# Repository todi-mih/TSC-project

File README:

Project for E-book made in fusion

Diagrama:
(its in the images folder)

_______
Hardware Modules Overview
ESP32-C6-WROOM-1-N8 – Core Microcontroller
Power Supply: 3.3V
Communication Protocols: SPI, I2C, UART, GPIO
Pin Mapping: Below, each module's interface is connected to the respective microcontroller pins.

USB-C Connector + ESD Protection
Main input for power and data transfer
TVS diodes included for electrostatic discharge (ESD) protection

LiPo Battery Fuel Gauge
Built-In charging controller
IC: MAX17048G+T10 for battery level monitoring
I2C Interface: SCL/SDA for communication with the Battery ChargeLevel IC
Qwiic / Stemma QT Connector for communication via I2C

Reset and Boot Buttons
BOOT: IO9
RESET: EN (Enable)
Reverse polarity protection diodes for safety

LDO Voltage Regulator
Converts 5V to 3.3V, providing power to the ESP32-C6 and connected peripherals

External Flash - NOR Flash 64MB
Connection Type: SPI
FLASH_CS: IO11
Shared SPI Lines: MOSI, MISO, SCK (with SD card and e-paper)

Environmental Sensor - BME688
Protocol: I2C (shared with RTC)
Voltage Supply: 3.3V
Pin Assignments: SDA, SCL

E-Paper Display
Connection Type: SPI
EPD_CS: IO10
EPD_DC: IO5
EPD_RST: IO23
EPD_BUSY: IO3
Shared SPI Lines: MOSI, SCK with SD Card

RTC Module - DS3231SN
Connection Type: I2C
SCL: IO22
SDA: IO21
INT_RTC: IO8
32KHZ: IO1
RTC_RST: IO18

SD Card Interface
Connection Type: SPI
SS_SD: IO4
MOSI: IO7
MISO: IO2
SCK: IO6

SPI Line Protection
Safeguards the SPI communication lines used by external modules like the SD card, e-paper display, and external flash
______

ESP32-C6 PINS
Protocol	ESP32-C6 Assigned Pins		Attached Devices
USB				GPIO13, GPIO12			Power supply & host communication
I2C				GPIO22, GPIO24			Environmental sensor (BME688), RTC, Battery voltage monitor
SPI			  GPIO7, GPIO2, GPIO6		E-paper display, NOR flash memory, SD storage
UART			GPIO16, GPIO17			Debugging / Firmware change
GPIO			GPIO0...GPIO23			Buttons, indicator outputs

BOM , links , datasheets
BUTTON_CUSYOMV1 https://eu.mouser.com/ProductDetail/Omron-Electronics/B3F-1000S?qs=C6KiJco3hx0Z3qfxWTJOrg%3D%3D
https://eu.mouser.com/datasheet/2/307/en_b3f-13826.pdf

100nF capacitor https://store.comet.srl.ro/Catalogue/Product/48939/ https://store.comet.bg/download-file.php?id=11
CPH3225A        https://eu.mouser.com/ProductDetail/Seiko-Semiconductors/CPH3225Aqs=3etwrb1wR%252BhUOph6lAO7eg%3D%3D
https://ro.mouser.com/datasheet/2/360/Seiko_Instruments_MicroBattery_E_20230330_2024Jan_-3561061.pdf
1.7uF capacitor https://store.comet.srl.ro/Catalogue/Product/5163462/ https://store.comet.bg/download-file.php?id=25117
USBLC6-2SC6Y    https://eu.mouser.com/ProductDetail/STMicroelectronics/USBLC6-2SC6Yqs=gNDSiZmRJS%2FOgDexvXkdow%3D%3D
https://ro.mouser.com/datasheet/2/389/usblc6_2sc6y-1852505.pdf
PGB1010603MR    https://eu.mouser.com/ProductDetail/Littelfuse/PGB1010603MR?qs=gu7KAQ731URLg4GSnNNN7Q%3D%3D
https://www.littelfuse.com/assetdocs/pulseguard-esd-suppressors-pgb1-datasheet?assetguid=8a337998-d54d-466b-be4e-dc5bcd1f9321
MBR0530         https://eu.mouser.com/ProductDetail/onsemi/MBR0530T3G?qs=3JMERSakebpEmdUS6GetdQ%3D%3D
https://www.littelfuse.com/assetdocs/pulseguard-esd-suppressors-pgb1-datasheet?assetguid=8a337998-d54d-466b-be4e-dc5bcd1f9321
TP20R           https://eu.mouser.com/ProductDetail/KOA-Speer/RN73R1ETTP20R0D50?qs=vLWxofP3U2xF4IfSiw9UAw%3D%3D
DS3231SN#       https://eu.mouser.com/ProductDetail/Analog-Devices-Maxim-Integrated/DS3231SN?qs=1eQvB6Dk1vhUlr8%2FOrV0Fw%3D%3D
https://www.koaspeer.com/pdfs/RN73R.pdf
W25Q512JVEIQ    https://eu.mouser.com/ProductDetail/Winbond/W25Q512JVEIQ?qs=l7cgNqFNU1jw6svr3at6tA%3D%3D
https://ro.mouser.com/datasheet/2/949/Winbond_W25Q512JV_Datasheet-3240039.pdf
MAX17048G+T10   https://eu.mouser.com/ProductDetail/Analog-Devices-Maxim-Integrated/MAX17048G%2bT10?qs=D7PJwyCwLAoGnnn8jEPRBQ%3D%3D
https://ro.mouser.com/datasheet/2/609/MAX17048_MAX17049-3469099.pdf
USBLC6-2SC6Y    https://eu.mouser.com/ProductDetail/STMicroelectronics/USBLC6-2SC6Y?qs=gNDSiZmRJS%2FOgDexvXkdow%3D%3D
https://ro.mouser.com/datasheet/2/389/usblc6_2sc6y-1852505.pdf
DMG2305UX-7     https://eu.mouser.com/ProductDetail/Diodes-Incorporated/DMG2305UX-7?qs=L1DZKBg7t5F%2FNBHrjfxC%252Bg%3D%3D
https://www.diodes.com/assets/Datasheets/DMG2305UX.pdf
XC6220A331MR-G  https://eu.mouser.com/ProductDetail/Torex-Semiconductor/XC6220A331MR-G?qs=AsjdqWjXhJ8ZSWznL1J0gg%3D%3D
https://ro.mouser.com/datasheet/2/760/xc6220-3371556.pdf
SI1308EDL-T1-BE3  https://eu.mouser.com/ProductDetail/Vishay-Siliconix/SI1308EDL-T1-BE3?qs=zW32dvEIR3shhEGZ2ACCcQ%3D%3D
https://www.vishay.com/doc?63399
MCP73831        https://eu.mouser.com/ProductDetail/Microchip-Technology/MCP73831T-2ACI-OT?qs=yUQqVecv4qvbBQBGbHx0Mw%3D%3D
https://ro.mouser.com/datasheet/2/268/MCP73831_Family_Data_Sheet_DS20001984H-3441711.pdf
ESP32-C6-WROOM-1-N8   https://eu.mouser.com/ProductDetail/Espressif-Systems/ESP32-C6-WROOM-1-N8?qs=8Wlm6%252BaMh8ST02Gmwp74cw%3D%3D
https://ro.mouser.com/datasheet/2/891/Espressif_ESP32_C6_WROOM_1__Datasheet_V0_1_PRELIMI-3239987.pdf
BD5229G     https://eu.mouser.com/ProductDetail/ROHM-Semiconductor/BD5229G-1TR?qs=sGAEpiMZZMutXGli8Ay4kGHG90gjHVFpj6WJfKJTe9w%3D
https://fscdn.rohm.com/en/products/databook/datasheet/ic/power/voltage_detector/bd52xxg-1-e.pdf
FH34SRJ-24S-0.5SH_99_   https://eu.mouser.com/ProductDetail/Hirose-Connector/FH34SRJ-24S-0.5SH50?qs=iyLo5FA4poC8fzWlavnA7A%3D%3D
https://ro.mouser.com/datasheet/2/185/FH34SRJ_24S_0_5SH_50__CL0580_1255_6_50_2DDrawing_0-1615030.pdf
BME688     https://eu.mouser.com/ProductDetail/Bosch-Sensortec/BME688?qs=IS%252B4QmGtzzqQoVDscqwx3A%3D%3D
https://ro.mouser.com/datasheet/2/783/bst_bme688_fl000-2307034.pdf

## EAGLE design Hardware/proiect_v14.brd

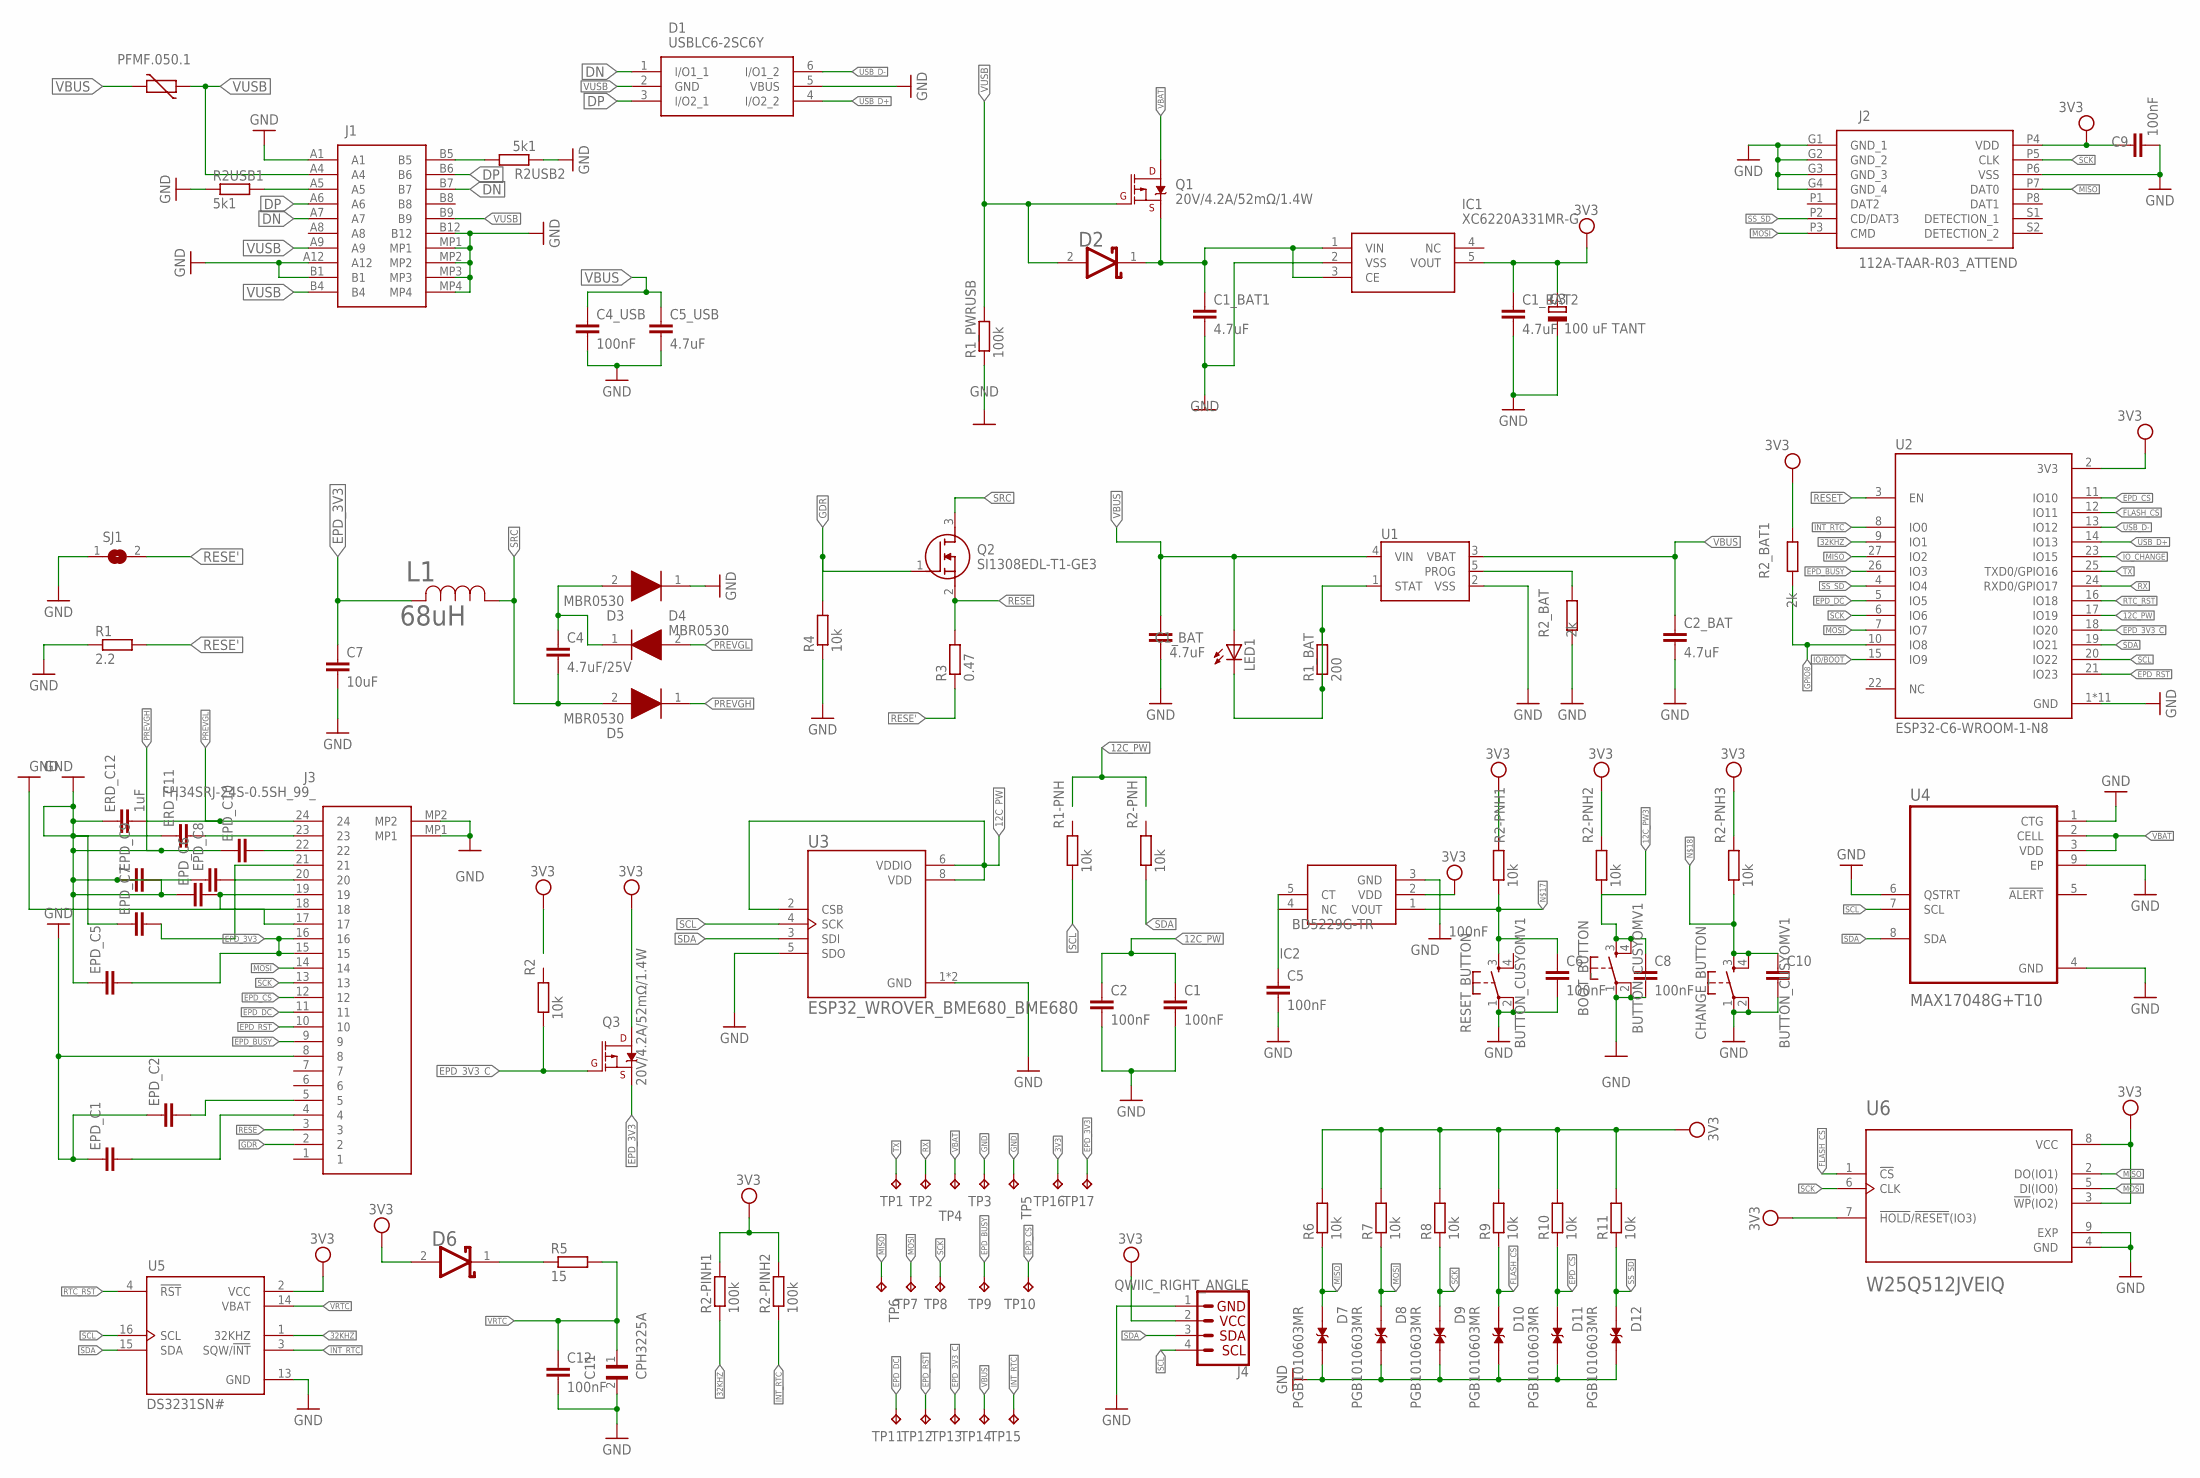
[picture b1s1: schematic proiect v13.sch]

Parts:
BOOT_BUTTON: BUTTON_CUSYOMV1; MYBUTTON
C1, C2, C4_USB, C5, C6, C8, C9, C10: 100nF; EAGLE-LTSPICE_C0402
C1_BAT, C1_BAT1, C1_BAT2, C2_BAT, C5_USB: 4.7uF; EAGLE-LTSPICE_C0402
C3: 100 uF TANT; RCL_CT3528
C4: 4.7uF/25V; EAGLE-LTSPICE_C0402
C7: 10uF; EAGLE-LTSPICE_C0402
C11: CPH3225A; CAPCP3225X100N
C12: 100nF; ESP32_WROVER_EAGLE-LTSPICE_C0402
CHANGE_BUTTON: BUTTON_CUSYOMV1; MYBUTTON
D1: USBLC6-2SC6Y; SOT95P280X145-6N
D2, D6: ESP32_WROVER_AVX---SD0805S020S1R0_AVX_SD0805S020S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; ESP32_WROVER_AVX---SD0805S020S1R0_AVX_SD0805S020S1R0_0
D3, D4, D5: MBR0530; SOD3716X135N
D7, D8, D9, D10, D11, D12: PGB1010603MR; DIOC1608X36N
EPD_C1, EPD_C2, EPD_C5, EPD_C6, EPD_C7, EPD_C8, EPD_C9: EAGLE-LTSPICE_CC0402; EAGLE-LTSPICE_C0402
EPD_C10: ESP32_WROVER_EAGLE-LTSPICE_CC0402; ESP32_WROVER_EAGLE-LTSPICE_C0402
ERD_C11: ESP32_WROVER_EAGLE-LTSPICE_CC0402; ESP32_WROVER_EAGLE-LTSPICE_C0402
ERD_C12: 1uF; ESP32_WROVER_EAGLE-LTSPICE_C0402
IC1: XC6220A331MR-G; SOT95P280X120-5N
IC2: BD5229G-TR; SOT95P280X125-5N
J1: SAMACSYS_PARTS_USB4110-GF-A; SAMACSYS_PARTS_USB4110GFA
J2: 112A-TAAR-R03_ATTEND; 112ATAARR03ATTEND
J3: FH34SRJ-24S-0.5SH_99_; FH34SRJ24S05SH99
J4: QWIIC_RIGHT_ANGLE; JST04_1MM_RA
L1: 68uH; IND_4828-WE-TPC_WRE
LED1: ADAFRUIT_LEDCHIP-LED0603; ADAFRUIT_CHIP-LED0603
PFMF.050.1: ESP32C6_VARISTORCN1812; ESP32C6_VARISTOR_CT/CN1812
Q1, Q3: 20V/4.2A/52mΩ/1.4W; ESP32_WROVER_SPARKFUN-DISCRETESEMI_SOT23-3
Q2: SI1308EDL-T1-GE3; SOT65P210X110-3N
R1: 2.2; ESP32_WROVER_EAGLE-LTSPICE_R0402
R1-PNH, R2, R2-PNH, R2-PNH1, R2-PNH2, R2-PNH3, R4, R6, R7, R8, R9, R10, R11: 10k; ESP32_WROVER_EAGLE-LTSPICE_R0402
R1_BAT: 200; ESP32_WROVER_EAGLE-LTSPICE_R0402
R1_PWRUSB, R2-PINH1, R2-PINH2: 100k; ESP32_WROVER_EAGLE-LTSPICE_R0402
R2USB1, R2USB2: 5k1; ESP32_WROVER_EAGLE-LTSPICE_R0402
R2_BAT, R2_BAT1: 2k; ESP32_WROVER_EAGLE-LTSPICE_R0402
R3: 0.47; ESP32_WROVER_EAGLE-LTSPICE_R0402
R5: 15; ESP32_WROVER_EAGLE-LTSPICE_R0402
RESET_BUTTON: BUTTON_CUSYOMV1; MYBUTTON
SJ1: SJ
TP1, TP2, TP3, TP4, TP5, TP6, TP7, TP8, TP9, TP10, TP11, TP12, TP13, TP14, TP15, TP16, TP17: TPTP20R; TP20R
U1: ESP32_WROVER_SPARKFUN-IC-POWER_MCP73831; ESP32_WROVER_SPARKFUN-IC-POWER_SOT23-5
U2: ESP32-C6-WROOM-1-N8; XCVR_ESP32-C6-WROOM-1-N8
U3: ESP32_WROVER_BME680_BME680; ESP32_WROVER_BME680_PSON80P300X300X100-8N
U4: MAX17048G+T10; SON50P200X200X80-9N
U5: DS3231SN#; SOIC127P1032X265-16N
U6: W25Q512JVEIQ; SON127P600X800X80-9N

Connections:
3V3: C1_BAT2.1, C3.+, C9.1, D6.2 (ANODE), IC1.5 (VOUT), IC2.2 (VDD), J2.P4 (VDD), J4.2, Q3.3 (D), R2-PINH1.2, R2-PINH2.2, R2-PNH1.2, R2-PNH2.2, R2-PNH3.2, R2_BAT1.2, R6.2, R7.2, R8.2, R9.2, R10.2, R11.2, TP16.TP, U2.2 (3V3), U5.2 (VCC), U6.3 (!WP!(IO2)), U6.7 (!HOLD!/!RESET!(IO3)), U6.8 (VCC)
12C_PW: C1.1, C2.1, U2.17 (IO19), U3.2 (CSB), U3.6 (VDDIO), U3.8 (VDD)
12C_PW1: C5.1, IC2.5 (CT)
12C_PW3: BOOT_BUTTON.3, BOOT_BUTTON.4, C8.1, R2-PNH2.1
32KHZ: R2-PINH1.1, U2.9 (IO1), U5.1 (32KHZ)
DN: J1.A7, J1.B6
DP: J1.A6, J1.B7
EPD_3V3: C7.1, EPD_C5.2, J3.15, J3.16, L1.2, Q3.2 (S), TP17.TP
EPD_3V3_C: Q3.1 (G), R2.1, TP13.TP, U2.18 (IO20)
EPD_BUSY: J3.9, TP9.TP, U2.26 (IO3)
EPD_CS: D11.1, J3.12, R10.1, TP10.TP, U2.11 (IO10)
EPD_DC: J3.11, TP11.TP, U2.5 (IO5)
EPD_RST: J3.10, TP12.TP, U2.21 (IO23)
FLASH_CS: D10.1, R9.1, U2.12 (IO11), U6.1 (!CS)
GDR: J3.2, Q2.1 (G), R4.2
GND: BOOT_BUTTON.1, BOOT_BUTTON.2, C1.2, C1_BAT.2, C1_BAT1.2, C1_BAT2.2, C2.2, C2_BAT.2, C3.-, C4_USB.2, C5.2, C5_USB.2, C6.2, C7.2, C8.2, C9.2, C10.2, C11.2, C12.2, CHANGE_BUTTON.1, CHANGE_BUTTON.2, D1.5 (VBUS), D3.1 (K), D7.2, D8.2, D9.2, D10.2, D11.2, D12.2, EPD_C1.1, EPD_C2.1, IC1.2 (VSS), IC2.3 (GND), J1.A1, J1.A12, J1.B1, J1.B12, J1.MP1, J1.MP2, J1.MP3, J1.MP4, J2.G1 (GND_1), J2.G2 (GND_2), J2.G3 (GND_3), J2.G4 (GND_4), J2.P6 (VSS), J3.8, J3.17, J3.MP1, J3.MP2, J4.1, R1.1, R1_PWRUSB.1, R2USB1.1, R2USB2.1, R2_BAT.1, R4.1, RESET_BUTTON.1, RESET_BUTTON.2, SJ1.1, TP3.TP, TP5.TP, U1.2 (VSS), U2.1 (GND), U2.28 (GND), U2.29_1 (GND), U2.29_2 (GND), U2.29_3 (GND), U2.29_4 (GND), U2.29_5 (GND), U2.29_6 (GND), U2.29_7 (GND), U2.29_8 (GND), U2.29_9 (GND), U3.1 (GND), U3.5 (SDO), U3.7 (GND), U4.1 (CTG), U4.4 (GND), U4.6 (QSTRT), U4.9 (EP), U5.13 (GND), U6.4 (GND), U6.9 (EXP)
GPIO8: R2_BAT1.1, U2.10 (IO8)
INT_RTC: R2-PINH2.1, TP15.TP, U2.8 (IO0), U5.3 (SQW/!INT)
IO/BOOT: U2.15 (IO9)
IO_CHANGE: U2.23 (IO15)
MISO: D7.1, J2.P7 (DAT0), R6.1, TP6.TP, U2.27 (IO2), U6.2 (DO(IO1))
MOSI: D8.1, J2.P3 (CMD), J3.14, R7.1, TP7.TP, U2.7 (IO7), U6.5 (DI(IO0))
unnamed: J1.A5, R2USB1.2
unnamed: J1.B5, R2USB2.2
unnamed: C4_USB.1, C5_USB.1
unnamed: C1_BAT1.1, D2.1 (CATHODE), IC1.1 (VIN), IC1.3 (CE), Q1.2 (S)
unnamed: D2.2 (ANODE), Q1.1 (G), R1_PWRUSB.2
unnamed: R2_BAT.2, U1.5 (PROG)
unnamed: C4.1, D3.2 (A), D4.1 (K)
unnamed: EPD_C1.2, J3.4
unnamed: EPD_C2.2, J3.5
unnamed: C6.1, IC2.1 (VOUT), R2-PNH1.1, RESET_BUTTON.3
unnamed: C10.1, CHANGE_BUTTON.3, CHANGE_BUTTON.4, R2-PNH3.1
unnamed: D6.1 (CATHODE), R5.1
unnamed: EPD_C8.2, J3.20
unnamed: EPD_C7.2, J3.21
unnamed: EPD_C6.2, J3.18, J3.19
unnamed: EPD_C10.2, J3.22
unnamed: ERD_C11.2, J3.23
PREVGH: D5.1 (K), EPD_C5.1, EPD_C6.1, EPD_C7.1, EPD_C8.1, EPD_C9.1, EPD_C9.2, EPD_C10.1, ERD_C11.1, ERD_C12.1
PREVGL: D4.2 (A), ERD_C12.2, J3.24
RESE: J3.3, Q2.2 (S), R3.2
RESE': R1.2, R3.1, SJ1.2
RESE'1: LED1.C, R1_BAT.1, R1_BAT.2, U1.1 (STAT)
RESET: U2.3 (EN)
RX: TP2.TP, U2.24 (RXD0/GPIO17)
SCK: D9.1, J2.P5 (CLK), J3.13, R8.1, TP8.TP, U2.6 (IO6), U6.6 (CLK)
SCL: J4.4, R1-PNH.1, U2.20 (IO22), U3.4 (SCK), U4.7 (SCL), U5.16 (SCL)
SDA: J4.3, R2-PNH.1, U2.19 (IO21), U3.3 (SDI), U4.8 (SDA), U5.15 (SDA)
SRC: C4.2, D5.2 (A), L1.1, Q2.3 (D)
SS_SD: D12.1, J2.P2 (CD/DAT3), R11.1, U2.4 (IO4)
TX: TP1.TP, U2.25 (TXD0/GPIO16)
VBAT: Q1.3 (D), TP4.TP, U4.2 (CELL), U4.3 (VDD)
VBUS: C1_BAT.1, C2_BAT.1, LED1.A, TP14.TP, U1.3 (VBAT), U1.4 (VIN)
VRTC: C11.1, C12.1, R5.2, U5.14 (VBAT)
VUSB: J1.A4, PFMF.050.1.1

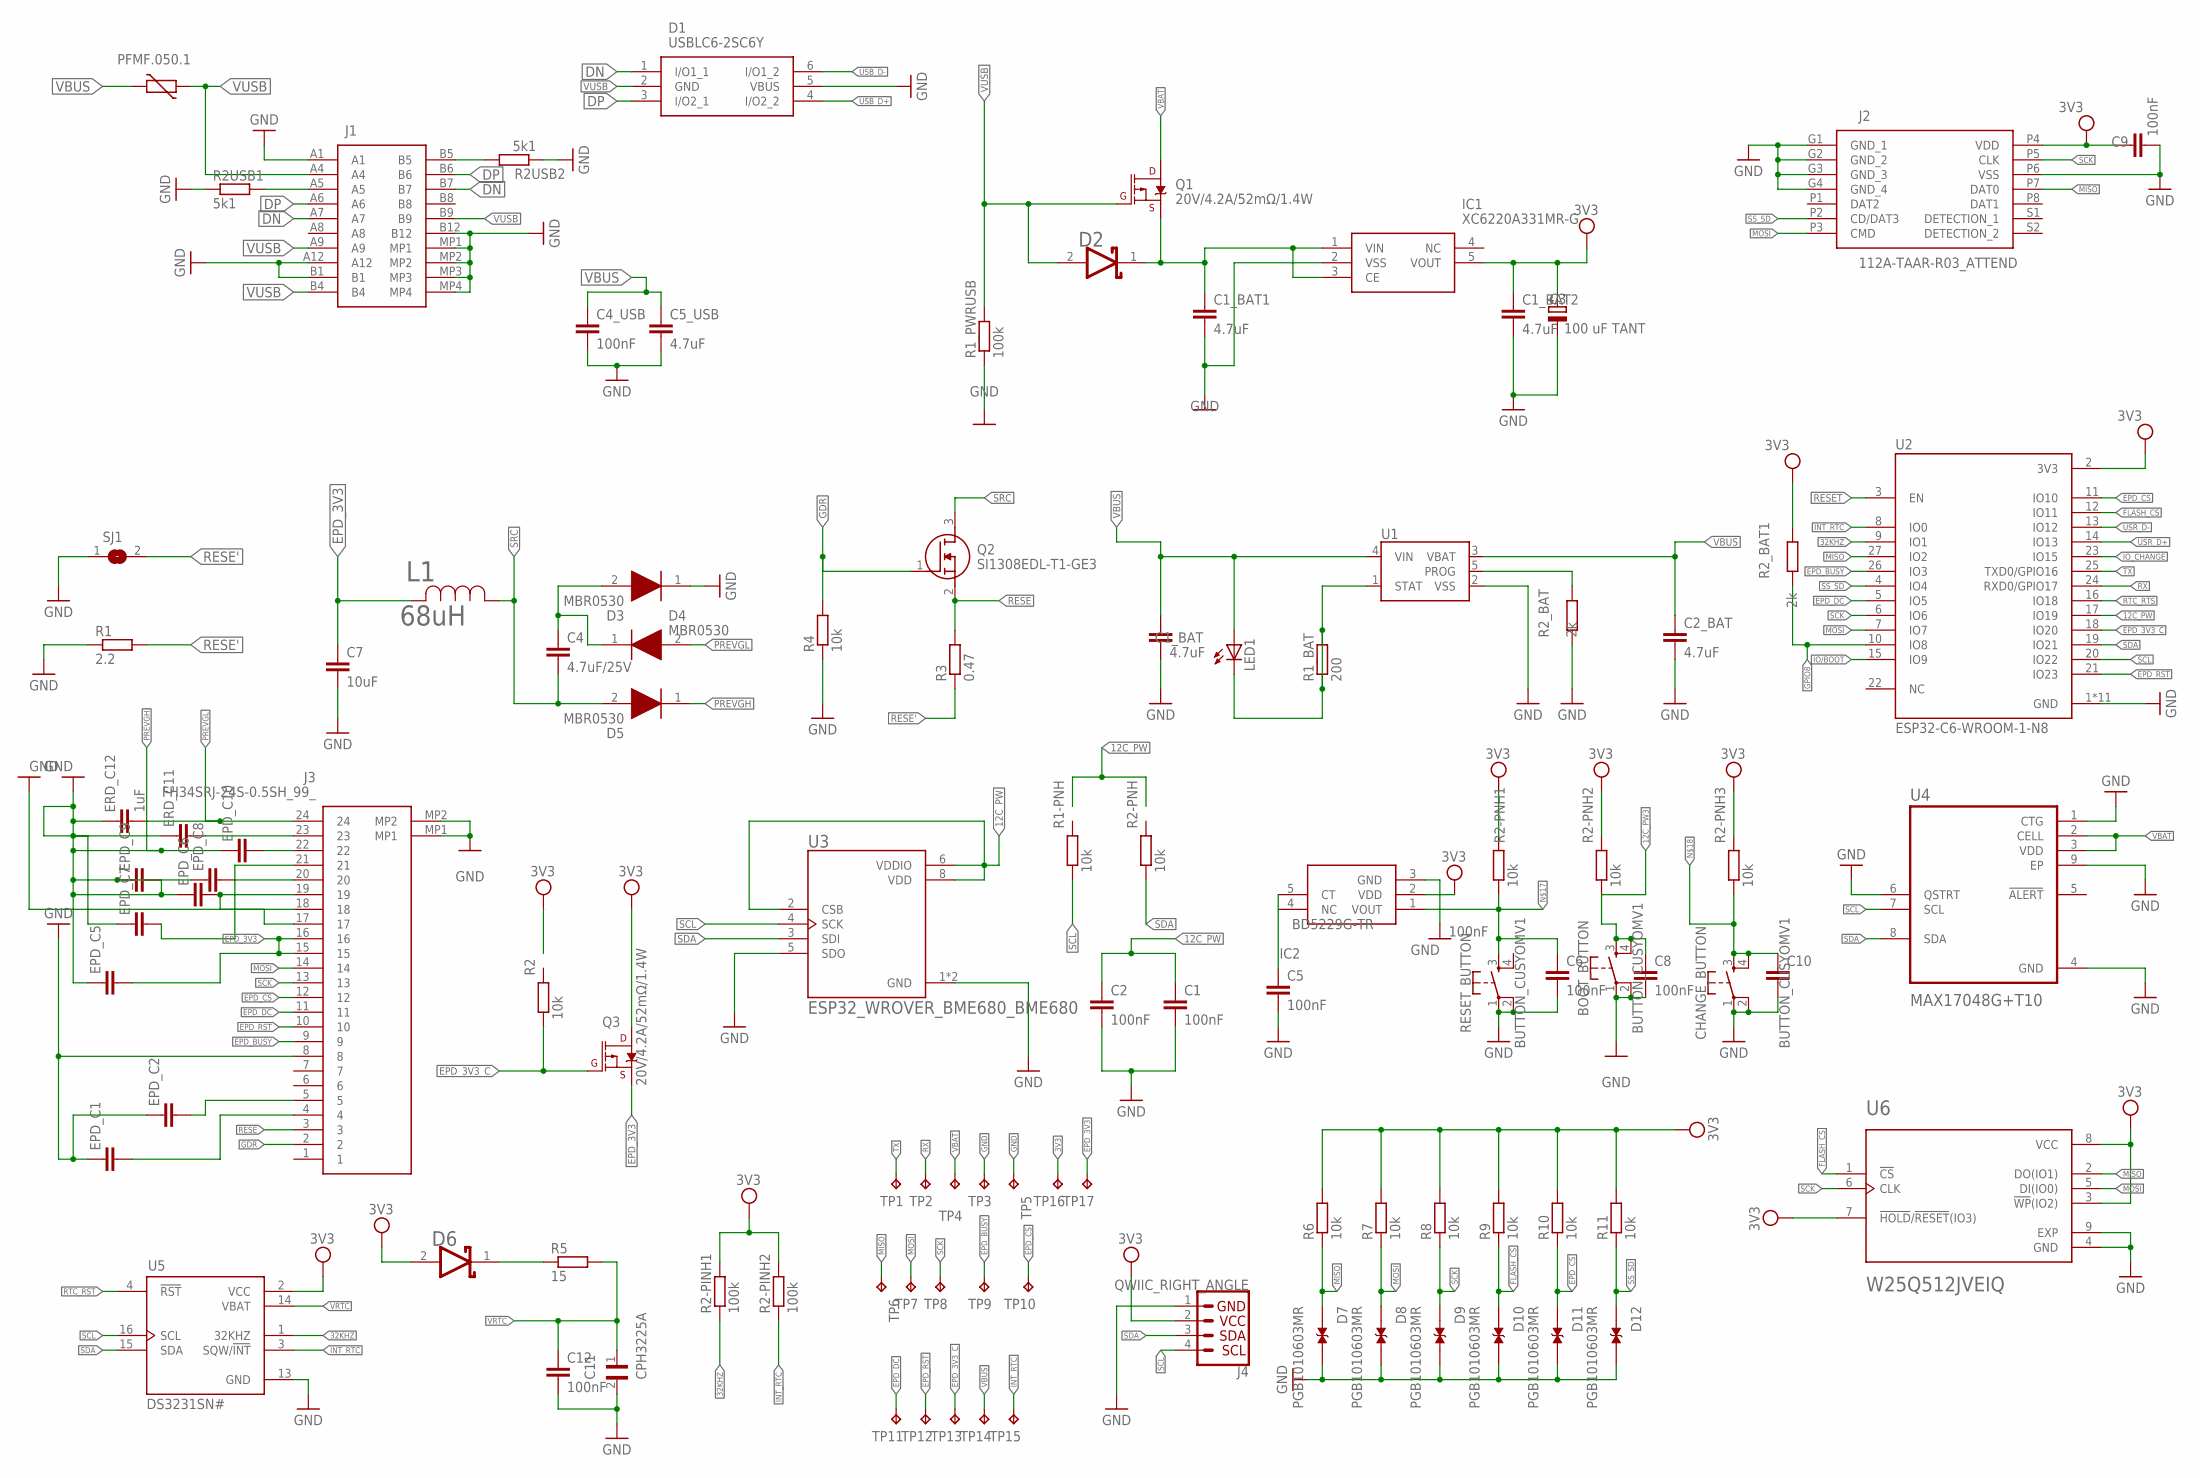
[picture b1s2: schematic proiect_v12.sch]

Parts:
BOOT_BUTTON: BUTTON_CUSYOMV1; MYBUTTON
C1, C2, C4_USB, C5, C6, C8, C9, C10: 100nF; EAGLE-LTSPICE_C0402
C1_BAT, C1_BAT1, C1_BAT2, C2_BAT, C5_USB: 4.7uF; EAGLE-LTSPICE_C0402
C3: 100 uF TANT; RCL_CT3528
C4: 4.7uF/25V; EAGLE-LTSPICE_C0402
C7: 10uF; EAGLE-LTSPICE_C0402
C11: CPH3225A; CAPCP3225X100N
C12: 100nF; ESP32_WROVER_EAGLE-LTSPICE_C0402
CHANGE_BUTTON: BUTTON_CUSYOMV1; MYBUTTON
D1: USBLC6-2SC6Y; SOT95P280X145-6N
D2, D6: ESP32_WROVER_AVX---SD0805S020S1R0_AVX_SD0805S020S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; ESP32_WROVER_AVX---SD0805S020S1R0_AVX_SD0805S020S1R0_0
D3, D4, D5: MBR0530; SOD3716X135N
D7, D8, D9, D10, D11, D12: PGB1010603MR; DIOC1608X36N
EPD_C1, EPD_C2, EPD_C5, EPD_C6, EPD_C7, EPD_C8, EPD_C9: EAGLE-LTSPICE_CC0402; EAGLE-LTSPICE_C0402
EPD_C10: ESP32_WROVER_EAGLE-LTSPICE_CC0402; ESP32_WROVER_EAGLE-LTSPICE_C0402
ERD_C11: ESP32_WROVER_EAGLE-LTSPICE_CC0402; ESP32_WROVER_EAGLE-LTSPICE_C0402
ERD_C12: 1uF; ESP32_WROVER_EAGLE-LTSPICE_C0402
IC1: XC6220A331MR-G; SOT95P280X120-5N
IC2: BD5229G-TR; SOT95P280X125-5N
J1: SAMACSYS_PARTS_USB4110-GF-A; SAMACSYS_PARTS_USB4110GFA
J2: 112A-TAAR-R03_ATTEND; 112ATAARR03ATTEND
J3: FH34SRJ-24S-0.5SH_99_; FH34SRJ24S05SH99
J4: QWIIC_RIGHT_ANGLE; JST04_1MM_RA
L1: 68uH; IND_4828-WE-TPC_WRE
LED1: ADAFRUIT_LEDCHIP-LED0603; ADAFRUIT_CHIP-LED0603
PFMF.050.1: ESP32C6_VARISTORCN1812; ESP32C6_VARISTOR_CT/CN1812
Q1, Q3: 20V/4.2A/52mΩ/1.4W; ESP32_WROVER_SPARKFUN-DISCRETESEMI_SOT23-3
Q2: SI1308EDL-T1-GE3; SOT65P210X110-3N
R1: 2.2; ESP32_WROVER_EAGLE-LTSPICE_R0402
R1-PNH, R2, R2-PNH, R2-PNH1, R2-PNH2, R2-PNH3, R4, R6, R7, R8, R9, R10, R11: 10k; ESP32_WROVER_EAGLE-LTSPICE_R0402
R1_BAT: 200; ESP32_WROVER_EAGLE-LTSPICE_R0402
R1_PWRUSB, R2-PINH1, R2-PINH2: 100k; ESP32_WROVER_EAGLE-LTSPICE_R0402
R2USB1, R2USB2: 5k1; ESP32_WROVER_EAGLE-LTSPICE_R0402
R2_BAT, R2_BAT1: 2k; ESP32_WROVER_EAGLE-LTSPICE_R0402
R3: 0.47; ESP32_WROVER_EAGLE-LTSPICE_R0402
R5: 15; ESP32_WROVER_EAGLE-LTSPICE_R0402
RESET_BUTTON: BUTTON_CUSYOMV1; MYBUTTON
SJ1: SJ
TP1, TP2, TP3, TP4, TP5, TP6, TP7, TP8, TP9, TP10, TP11, TP12, TP13, TP14, TP15, TP16, TP17: TPTP20R; TP20R
U1: ESP32_WROVER_SPARKFUN-IC-POWER_MCP73831; ESP32_WROVER_SPARKFUN-IC-POWER_SOT23-5
U2: ESP32-C6-WROOM-1-N8; XCVR_ESP32-C6-WROOM-1-N8
U3: ESP32_WROVER_BME680_BME680; ESP32_WROVER_BME680_PSON80P300X300X100-8N
U4: MAX17048G+T10; SON50P200X200X80-9N
U5: DS3231SN#; SOIC127P1032X265-16N
U6: W25Q512JVEIQ; SON127P600X800X80-9N

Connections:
3V3: C1_BAT2.1, C3.+, C9.1, D6.2 (ANODE), IC1.5 (VOUT), IC2.2 (VDD), J2.P4 (VDD), J4.2, Q3.3 (D), R2-PINH1.2, R2-PINH2.2, R2-PNH1.2, R2-PNH2.2, R2-PNH3.2, R2_BAT1.2, R6.2, R7.2, R8.2, R9.2, R10.2, R11.2, TP16.TP, U2.2 (3V3), U5.2 (VCC), U6.3 (!WP!(IO2)), U6.7 (!HOLD!/!RESET!(IO3)), U6.8 (VCC)
12C_PW: C1.1, C2.1, U2.17 (IO19), U3.2 (CSB), U3.6 (VDDIO), U3.8 (VDD)
12C_PW1: C5.1, IC2.5 (CT)
12C_PW3: BOOT_BUTTON.3, BOOT_BUTTON.4, C8.1, R2-PNH2.1
32KHZ: R2-PINH1.1, U2.9 (IO1), U5.1 (32KHZ)
DN: J1.A7, J1.B6
DP: J1.A6, J1.B7
EPD_3V3: C7.1, EPD_C5.2, J3.15, J3.16, L1.2, Q3.2 (S), TP17.TP
EPD_3V3_C: Q3.1 (G), R2.1, TP13.TP, U2.18 (IO20)
EPD_BUSY: J3.9, TP9.TP, U2.26 (IO3)
EPD_CS: D11.1, J3.12, R10.1, TP10.TP, U2.11 (IO10)
EPD_DC: J3.11, TP11.TP, U2.5 (IO5)
EPD_RST: J3.10, TP12.TP, U2.21 (IO23)
FLASH_CS: D10.1, R9.1, U2.12 (IO11), U6.1 (!CS)
GDR: J3.2, Q2.1 (G), R4.2
GND: BOOT_BUTTON.1, BOOT_BUTTON.2, C1.2, C1_BAT.2, C1_BAT1.2, C1_BAT2.2, C2.2, C2_BAT.2, C3.-, C4_USB.2, C5.2, C5_USB.2, C6.2, C7.2, C8.2, C9.2, C10.2, C11.2, C12.2, CHANGE_BUTTON.1, CHANGE_BUTTON.2, D1.5 (VBUS), D3.1 (K), D7.2, D8.2, D9.2, D10.2, D11.2, D12.2, EPD_C1.1, EPD_C2.1, IC1.2 (VSS), IC2.3 (GND), J1.A1, J1.A12, J1.B1, J1.B12, J1.MP1, J1.MP2, J1.MP3, J1.MP4, J2.G1 (GND_1), J2.G2 (GND_2), J2.G3 (GND_3), J2.G4 (GND_4), J2.P6 (VSS), J3.8, J3.17, J3.MP1, J3.MP2, J4.1, R1.1, R1_PWRUSB.1, R2USB1.1, R2USB2.1, R2_BAT.1, R4.1, RESET_BUTTON.1, RESET_BUTTON.2, SJ1.1, TP3.TP, TP5.TP, U1.2 (VSS), U2.1 (GND), U2.28 (GND), U2.29_1 (GND), U2.29_2 (GND), U2.29_3 (GND), U2.29_4 (GND), U2.29_5 (GND), U2.29_6 (GND), U2.29_7 (GND), U2.29_8 (GND), U2.29_9 (GND), U3.1 (GND), U3.5 (SDO), U3.7 (GND), U4.1 (CTG), U4.4 (GND), U4.6 (QSTRT), U4.9 (EP), U5.13 (GND), U6.4 (GND), U6.9 (EXP)
GPIO8: R2_BAT1.1, U2.10 (IO8)
INT_RTC: R2-PINH2.1, TP15.TP, U2.8 (IO0), U5.3 (SQW/!INT)
IO/BOOT: U2.15 (IO9)
IO_CHANGE: U2.23 (IO15)
MISO: D7.1, J2.P7 (DAT0), R6.1, TP6.TP, U2.27 (IO2), U6.2 (DO(IO1))
MOSI: D8.1, J2.P3 (CMD), J3.14, R7.1, TP7.TP, U2.7 (IO7), U6.5 (DI(IO0))
unnamed: J1.A5, R2USB1.2
unnamed: J1.B5, R2USB2.2
unnamed: C4_USB.1, C5_USB.1
unnamed: C1_BAT1.1, D2.1 (CATHODE), IC1.1 (VIN), IC1.3 (CE), Q1.2 (S)
unnamed: D2.2 (ANODE), Q1.1 (G), R1_PWRUSB.2
unnamed: R2_BAT.2, U1.5 (PROG)
unnamed: C4.1, D3.2 (A), D4.1 (K)
unnamed: EPD_C1.2, J3.4
unnamed: EPD_C2.2, J3.5
unnamed: C6.1, IC2.1 (VOUT), R2-PNH1.1, RESET_BUTTON.3
unnamed: C10.1, CHANGE_BUTTON.3, CHANGE_BUTTON.4, R2-PNH3.1
unnamed: D6.1 (CATHODE), R5.1
unnamed: EPD_C8.2, J3.20
unnamed: EPD_C7.2, J3.21
unnamed: EPD_C6.2, J3.18, J3.19
unnamed: EPD_C10.2, J3.22
unnamed: ERD_C11.2, J3.23
PREVGH: D5.1 (K), EPD_C5.1, EPD_C6.1, EPD_C7.1, EPD_C8.1, EPD_C9.1, EPD_C9.2, EPD_C10.1, ERD_C11.1, ERD_C12.1
PREVGL: D4.2 (A), ERD_C12.2, J3.24
RESE: J3.3, Q2.2 (S), R3.2
RESE': R1.2, R3.1, SJ1.2
RESE'1: LED1.C, R1_BAT.1, R1_BAT.2, U1.1 (STAT)
RESET: U2.3 (EN)
RX: TP2.TP, U2.24 (RXD0/GPIO17)
SCK: D9.1, J2.P5 (CLK), J3.13, R8.1, TP8.TP, U2.6 (IO6), U6.6 (CLK)
SCL: J4.4, R1-PNH.1, U2.20 (IO22), U3.4 (SCK), U4.7 (SCL), U5.16 (SCL)
SDA: J4.3, R2-PNH.1, U2.19 (IO21), U3.3 (SDI), U4.8 (SDA), U5.15 (SDA)
SRC: C4.2, D5.2 (A), L1.1, Q2.3 (D)
SS_SD: D12.1, J2.P2 (CD/DAT3), R11.1, U2.4 (IO4)
TX: TP1.TP, U2.25 (TXD0/GPIO16)
VBAT: Q1.3 (D), TP4.TP, U4.2 (CELL), U4.3 (VDD)
VBUS: C1_BAT.1, C2_BAT.1, LED1.A, TP14.TP, U1.3 (VBAT), U1.4 (VIN)
VRTC: C11.1, C12.1, R5.2, U5.14 (VBAT)
VUSB: J1.A4, PFMF.050.1.1

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
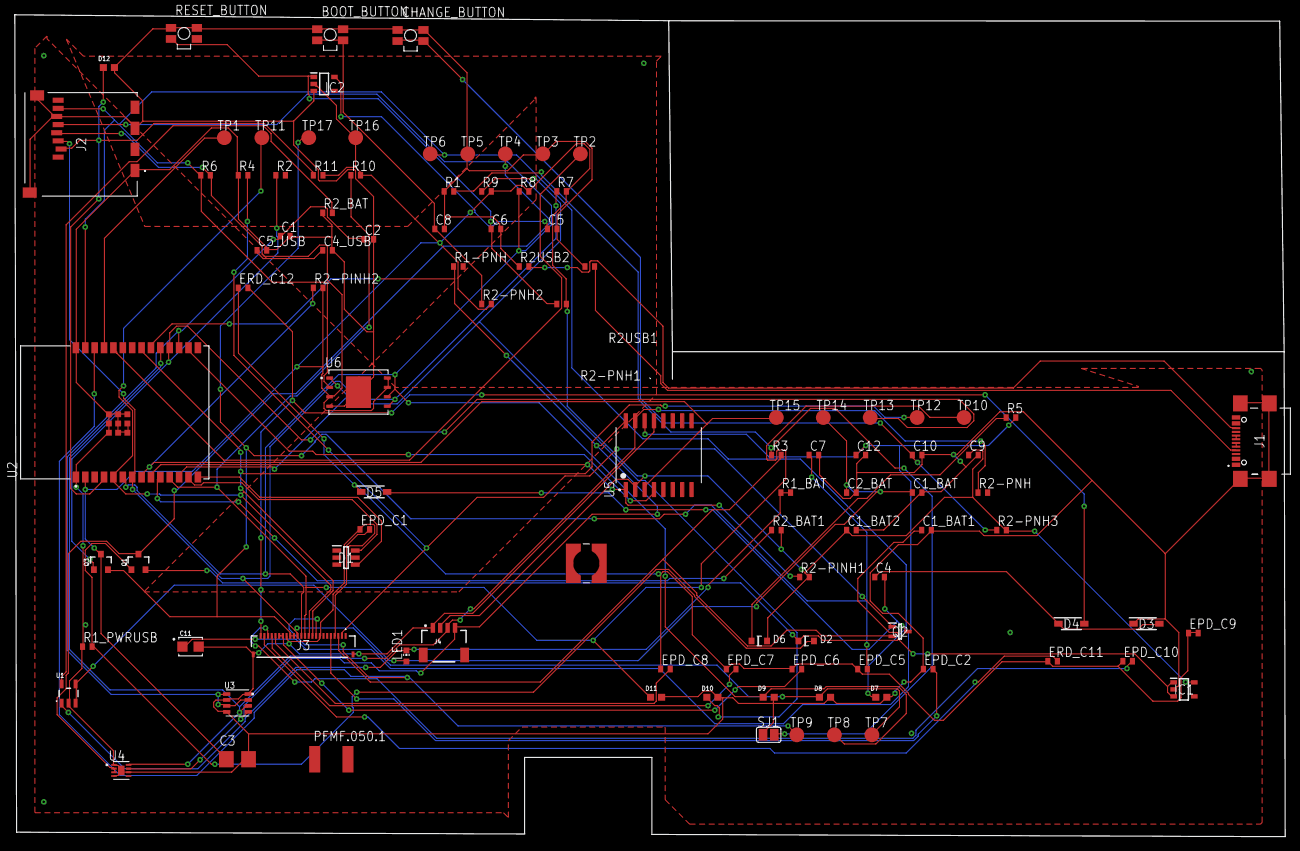
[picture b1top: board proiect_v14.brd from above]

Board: 2 copper layers, 171.9 x 111.2 mm, 103 parts (0 on the bottom side), 56 nets.

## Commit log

2025-04-05 Final commit - ready for public
2025-04-05 readme
2025-04-11 added datasheets
2025-04-11 Add files via upload
    new fixed scheme
2025-04-11 Add files via upload
    improved pcb
2025-04-11 Add files via upload
    new photos of improved boards
2025-04-11 Add files via upload
    fixed .step file and .step file for the pcb
2025-04-11 Add files via upload
    Added GND planes and via switching

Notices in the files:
parts and their libraries:
DeskAssistant v19 v1: COPYRIGHT: Copyright (C) 2024 Ultra Librarian. All rights reserved.
